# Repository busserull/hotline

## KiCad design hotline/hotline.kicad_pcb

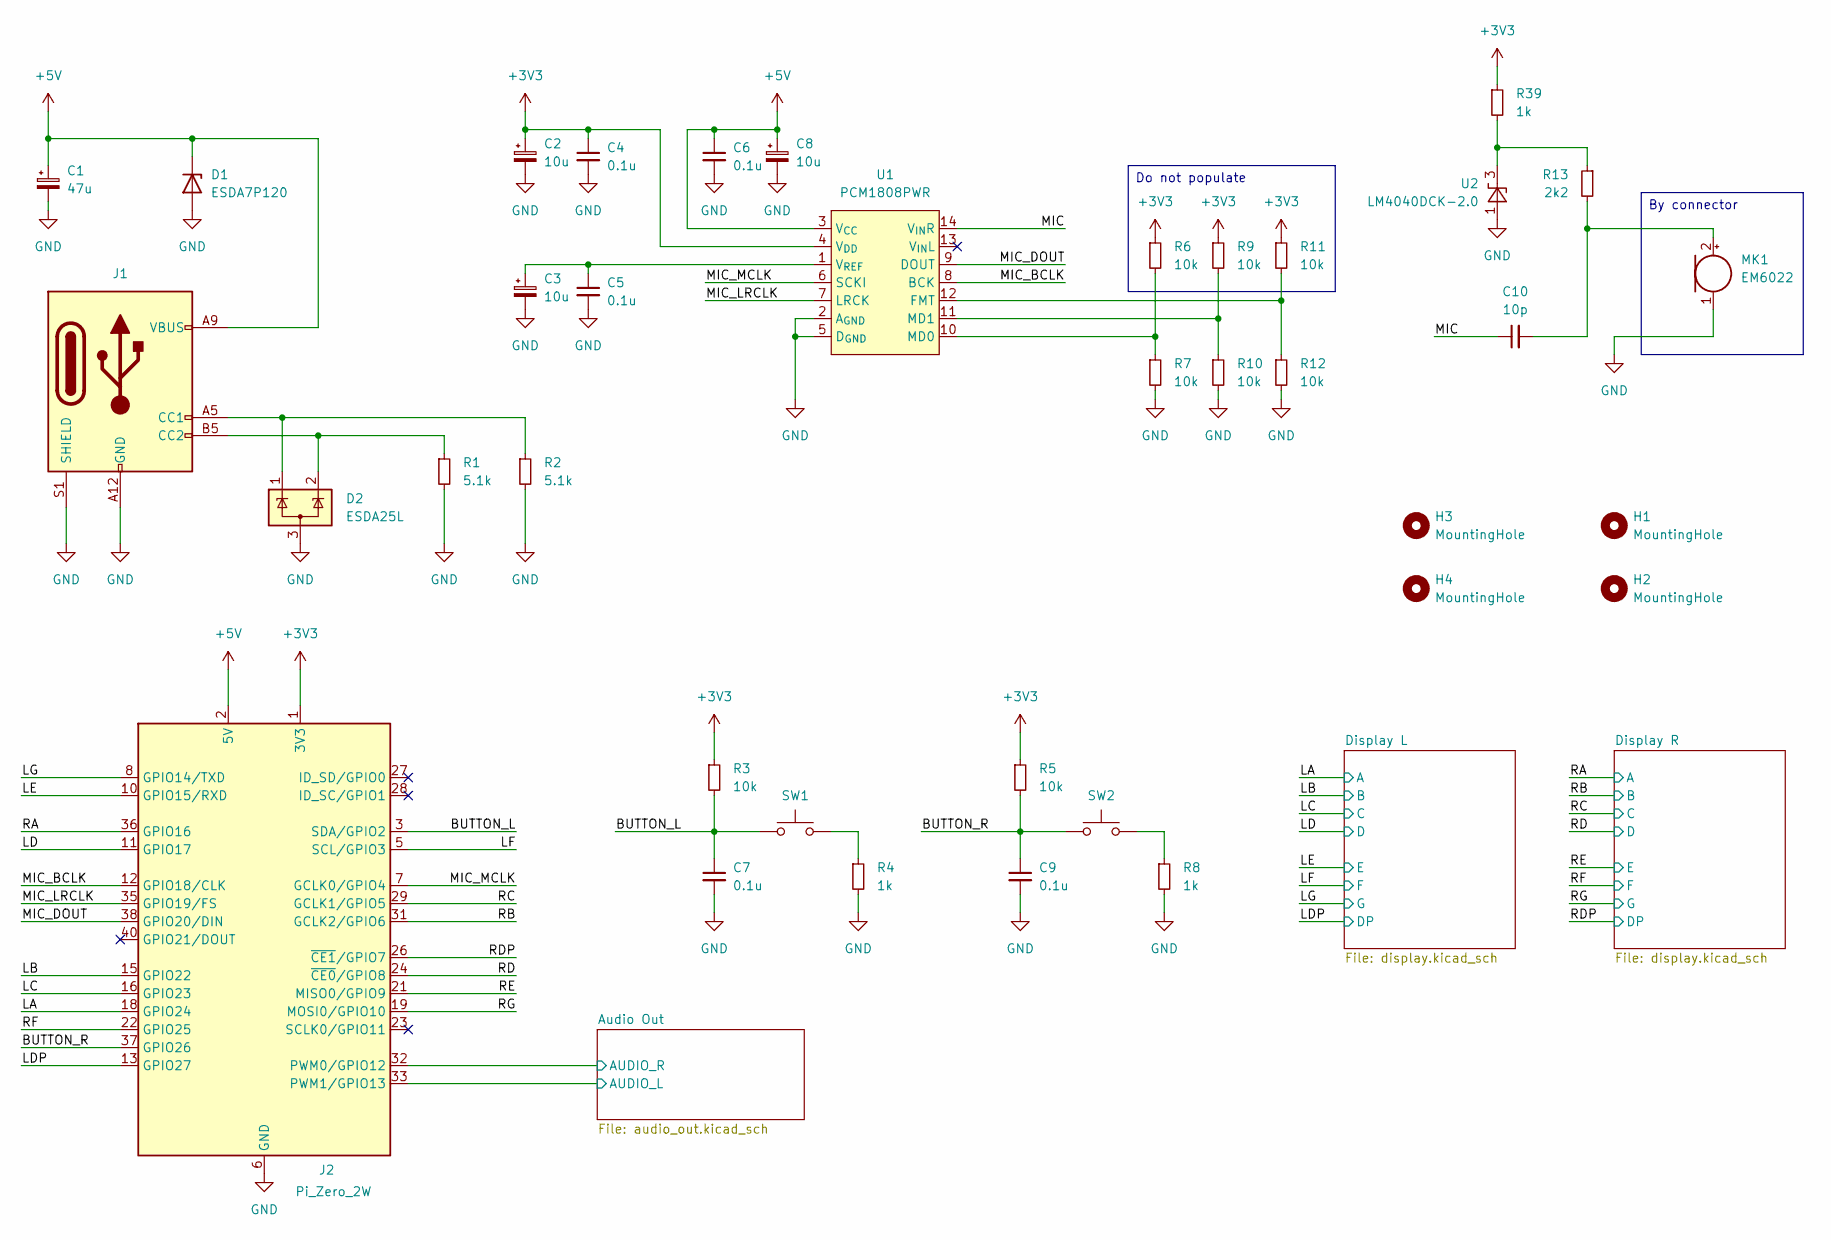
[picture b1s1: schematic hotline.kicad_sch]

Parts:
C1: 47u; CP_Elec_6.3x7.7
C2, C3, C8: 10u; CP_Elec_4x5.7
C4, C5, C6, C7, C9: 0.1u; C_0603_1608Metric_Pad1.08x0.95mm_HandSolder
C10: 10p; C_0603_1608Metric_Pad1.08x0.95mm_HandSolder
D1: ESDA7P120; D_0603_1608Metric_Pad1.05x0.95mm_HandSolder
D2: ESDA25L; SOT-23-3
H1, H2, H3, H4: MountingHole; MountingHole_2.2mm_M2_ISO7380_Pad
J1: USB_C_Receptacle_PowerOnly_24P; USB_C_Receptacle_HRO_TYPE-C-31-M-17
J2: Pi_Zero_2W; PinHeader_2x20_P2.54mm_Vertical
MK1: EM6022; TerminalBlock_Phoenix_PT-1,5-2-5.0-H_1x02_P5.00mm_Horizontal
R1, R2: 5.1k; R_0603_1608Metric_Pad0.98x0.95mm_HandSolder
R3, R5, R6, R7, R9, R10, R11, R12: 10k; R_0603_1608Metric_Pad0.98x0.95mm_HandSolder
R4, R8, R39: 1k; R_0603_1608Metric_Pad0.98x0.95mm_HandSolder
R13: 2k2; R_0603_1608Metric_Pad0.98x0.95mm_HandSolder
SW1: Left; TerminalBlock_Phoenix_PT-1,5-2-5.0-H_1x02_P5.00mm_Horizontal
SW2: Right; TerminalBlock_Phoenix_PT-1,5-2-5.0-H_1x02_P5.00mm_Horizontal
U1: PCM1808PWR; TSSOP-14_4.4x5mm_P0.65mm
U2: LM4040DCK-2.0; SOT-353_SC-70-5

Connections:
+3V3: C2.1, C4.1, J2.1 (3V3), J2.17 (3V3), R3.1, R5.1, R6.1, R9.1, R11.1, R39.1, U1.4 (V_{DD}); also elsewhere on the board
+5V: C1.1, C6.1, C8.1, D1.1 (K), J1.A4 (VBUS), J1.A9 (VBUS), J1.B4 (VBUS), J1.B9 (VBUS), J2.2 (5V), J2.4 (5V), U1.3 (V_{CC}); also elsewhere on the board
/Audio Out/AUDIO_L: J2.33 (PWM1/GPIO13); also elsewhere on the board
/Audio Out/AUDIO_R: J2.32 (PWM0/GPIO12); also elsewhere on the board
/BUTTON_L: C7.1, J2.3 (SDA/GPIO2), R3.2, SW1.1
/BUTTON_R: C9.1, J2.37 (GPIO26), R5.2, SW2.1
/LA: J2.18 (GPIO24); also elsewhere on the board
/LB: J2.15 (GPIO22); also elsewhere on the board
/LC: J2.16 (GPIO23); also elsewhere on the board
/LD: J2.11 (GPIO17); also elsewhere on the board
/LDP: J2.13 (GPIO27); also elsewhere on the board
/LE: J2.10 (GPIO15/RXD); also elsewhere on the board
/LF: J2.5 (SCL/GPIO3); also elsewhere on the board
/LG: J2.8 (GPIO14/TXD); also elsewhere on the board
/MIC: C10.1, U1.14 (V_{IN}R)
/MIC_BCLK: J2.12 (GPIO18/CLK), U1.8 (BCK)
/MIC_DOUT: J2.38 (GPIO20/DIN), U1.9 (DOUT)
/MIC_LRCLK: J2.35 (GPIO19/FS), U1.7 (LRCK)
/MIC_MCLK: J2.7 (GCLK0/GPIO4), U1.6 (SCKI)
/RA: J2.36 (GPIO16); also elsewhere on the board
/RB: J2.31 (GCLK2/GPIO6); also elsewhere on the board
/RC: J2.29 (GCLK1/GPIO5); also elsewhere on the board
/RD: J2.24 (~CE0/GPIO8); also elsewhere on the board
/RDP: J2.26 (~CE1/GPIO7); also elsewhere on the board
/RE: J2.21 (MISO0/GPIO9); also elsewhere on the board
/RF: J2.22 (GPIO25); also elsewhere on the board
/RG: J2.19 (MOSI0/GPIO10); also elsewhere on the board
GND: C1.2, C2.2, C3.2, C4.2, C5.2, C6.2, C7.2, C8.2, C9.2, D1.2 (A), D2.3 (A), J1.A1 (GND), J1.A12 (GND), J1.B1 (GND), J1.B12 (GND), J1.S1 (SHIELD), J2.6 (GND), J2.9 (GND), J2.14 (GND), J2.20 (GND), J2.25 (GND), J2.30 (GND), J2.34 (GND), J2.39 (GND), MK1.1 (-), R1.2, R2.2, R4.2, R7.2, R8.2, R10.2, R12.2, U1.2 (A_{GND}), U1.5 (D_{GND}), U2.1 (A); also elsewhere on the board
unnamed: D2.1 (K), J1.A5 (CC1), R2.1
unnamed: D2.2 (K), J1.B5 (CC2), R1.1
unnamed: C10.2, MK1.2 (+), R13.2
unnamed: R4.1, SW1.2
unnamed: R8.1, SW2.2
unnamed: R11.2, R12.1, U1.12 (FMT)
unnamed: R6.2, R7.1, U1.10 (MD0)
unnamed: R9.2, R10.1, U1.11 (MD1)
unnamed: C3.1, C5.1, U1.1 (V_{REF})
unnamed: R13.1, R39.2, U2.3 (K)

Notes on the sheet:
By connector
Do not populate

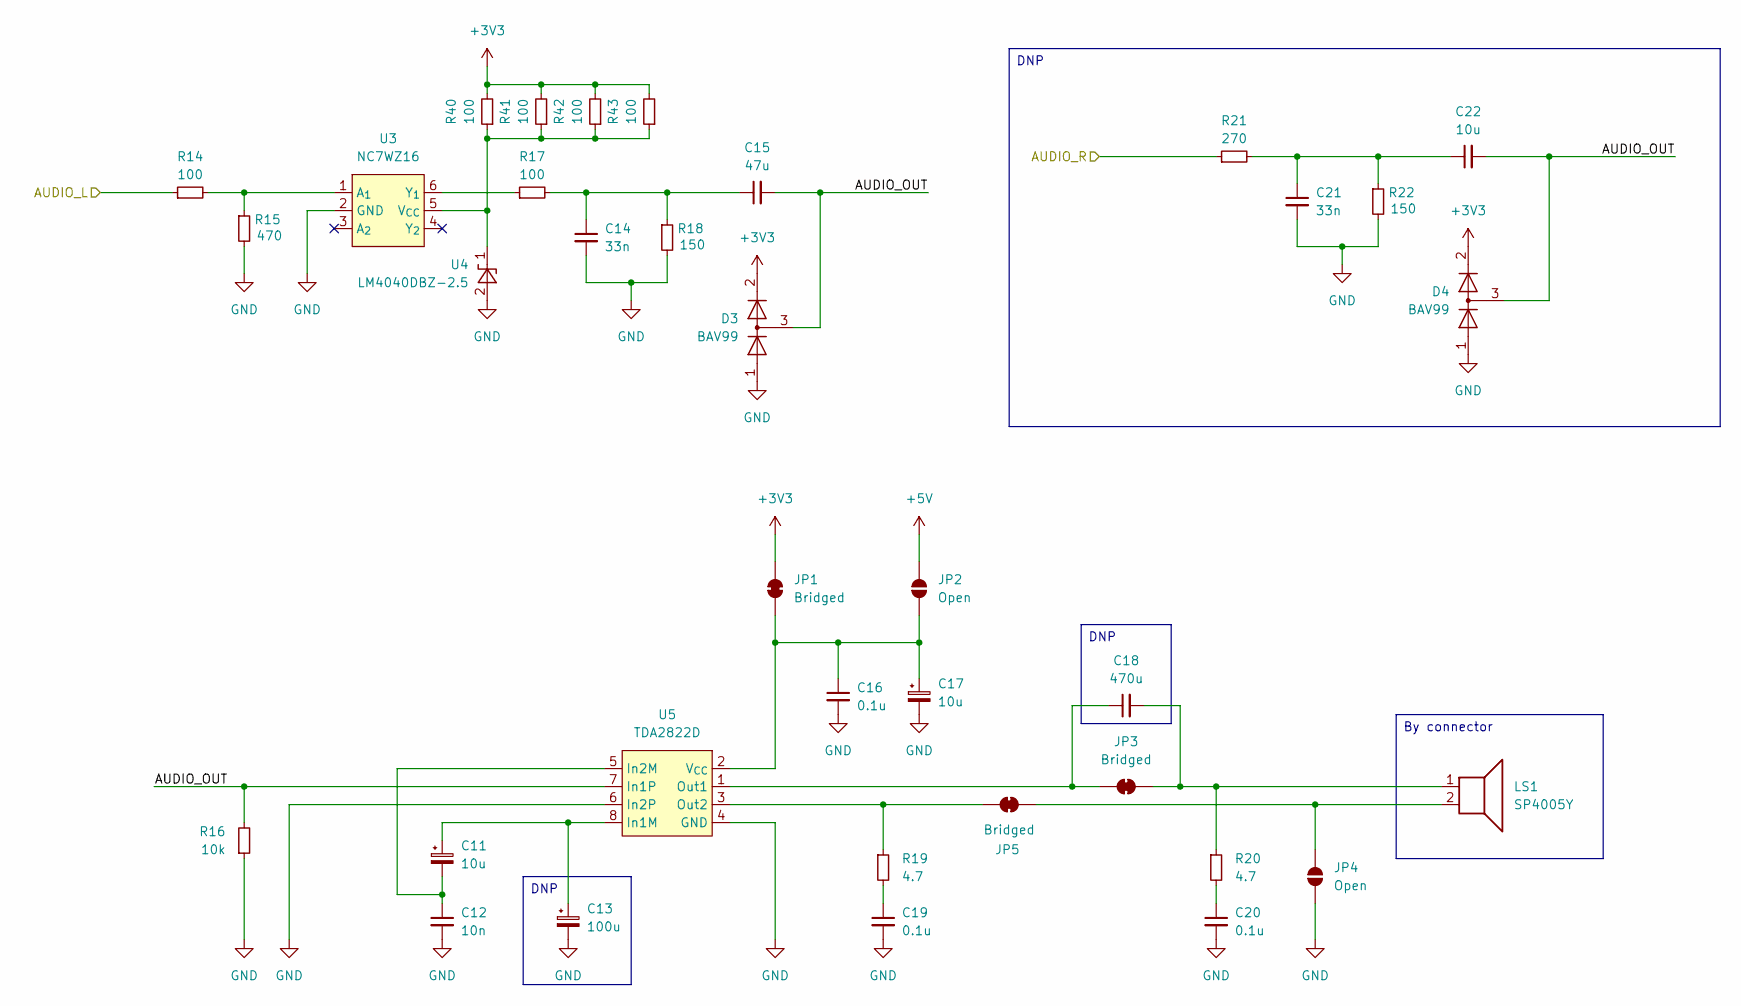
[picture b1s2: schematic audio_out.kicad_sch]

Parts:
C11, C17: 10u; CP_Elec_4x5.7
C12: 10n; C_0603_1608Metric_Pad1.08x0.95mm_HandSolder
C13: 100u; CP_Elec_5x5.3
C14, C21: 33n; C_0603_1608Metric_Pad1.08x0.95mm_HandSolder
C15: 47u; C_0805_2012Metric_Pad1.18x1.45mm_HandSolder
C16, C19, C20: 0.1u; C_0603_1608Metric_Pad1.08x0.95mm_HandSolder
C18: 470u; CP_Elec_8x10
C22: 10u; C_0805_2012Metric_Pad1.18x1.45mm_HandSolder
D3, D4: BAV99; SOT-23
JP1, JP3, JP5: Bridged; SolderJumper-2_P1.3mm_Bridged_RoundedPad1.0x1.5mm
JP2, JP4: Open; SolderJumper-2_P1.3mm_Open_RoundedPad1.0x1.5mm
LS1: SP4005Y; TerminalBlock_Phoenix_PT-1,5-2-5.0-H_1x02_P5.00mm_Horizontal
R14, R17, R40, R41, R42, R43: 100; R_0603_1608Metric_Pad0.98x0.95mm_HandSolder
R15: 470; R_0603_1608Metric_Pad0.98x0.95mm_HandSolder
R16: 10k; R_0603_1608Metric_Pad0.98x0.95mm_HandSolder
R18, R22: 150; R_0603_1608Metric_Pad0.98x0.95mm_HandSolder
R19, R20: 4.7; R_0603_1608Metric_Pad0.98x0.95mm_HandSolder
R21: 270; R_0603_1608Metric_Pad0.98x0.95mm_HandSolder
U3: NC7WZ16; SOT-363_SC-70-6_Handsoldering
U4: LM4040DBZ-2.5; SOT-23
U5: TDA2822D; SOIC-8_3.9x4.9mm_P1.27mm

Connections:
+3V3: D3.2 (A), D4.2 (A), JP1.2 (B), R40.2, R41.2, R42.2, R43.2; also elsewhere on the board
+5V: JP2.2 (B); also elsewhere on the board
/Audio Out/AUDIO_L: R14.1; also elsewhere on the board
/Audio Out/AUDIO_OUT: C15.2, C22.2, D3.3 (K), D4.3 (K), R16.2, U5.7 (In1P)
/Audio Out/AUDIO_R: R21.1; also elsewhere on the board
GND: C12.2, C13.2, C14.2, C16.2, C17.2, C19.2, C20.2, C21.2, D3.1 (K), D4.1 (K), JP4.1 (A), R15.2, R16.1, R18.2, R22.2, U3.2 (GND), U4.2 (A), U5.4 (GND), U5.6 (In2P); also elsewhere on the board
unnamed: C14.1, C15.1, R17.2, R18.1
unnamed: C19.1, R19.2
unnamed: C20.1, R20.2
unnamed: C21.1, C22.1, R21.2, R22.1
unnamed: C16.1, C17.1, JP1.1 (A), JP2.1 (A), U5.2 (V_{CC})
unnamed: C18.2, JP3.1 (A), LS1.1, R20.1
unnamed: C18.1, JP3.2 (B), U5.1 (Out1)
unnamed: JP4.2 (B), JP5.1 (A), LS1.2
unnamed: JP5.2 (B), R19.1, U5.3 (Out2)
unnamed: R14.2, R15.1, U3.1 (A_{1})
unnamed: R40.1, R41.1, R42.1, R43.1, U3.5 (V_{CC}), U4.1 (K)
unnamed: R17.1, U3.6 (Y_{1})
unnamed: C11.1, C13.1, U5.8 (In1M)
unnamed: C11.2, C12.1, U5.5 (In2M)

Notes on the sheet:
DNP
By connector

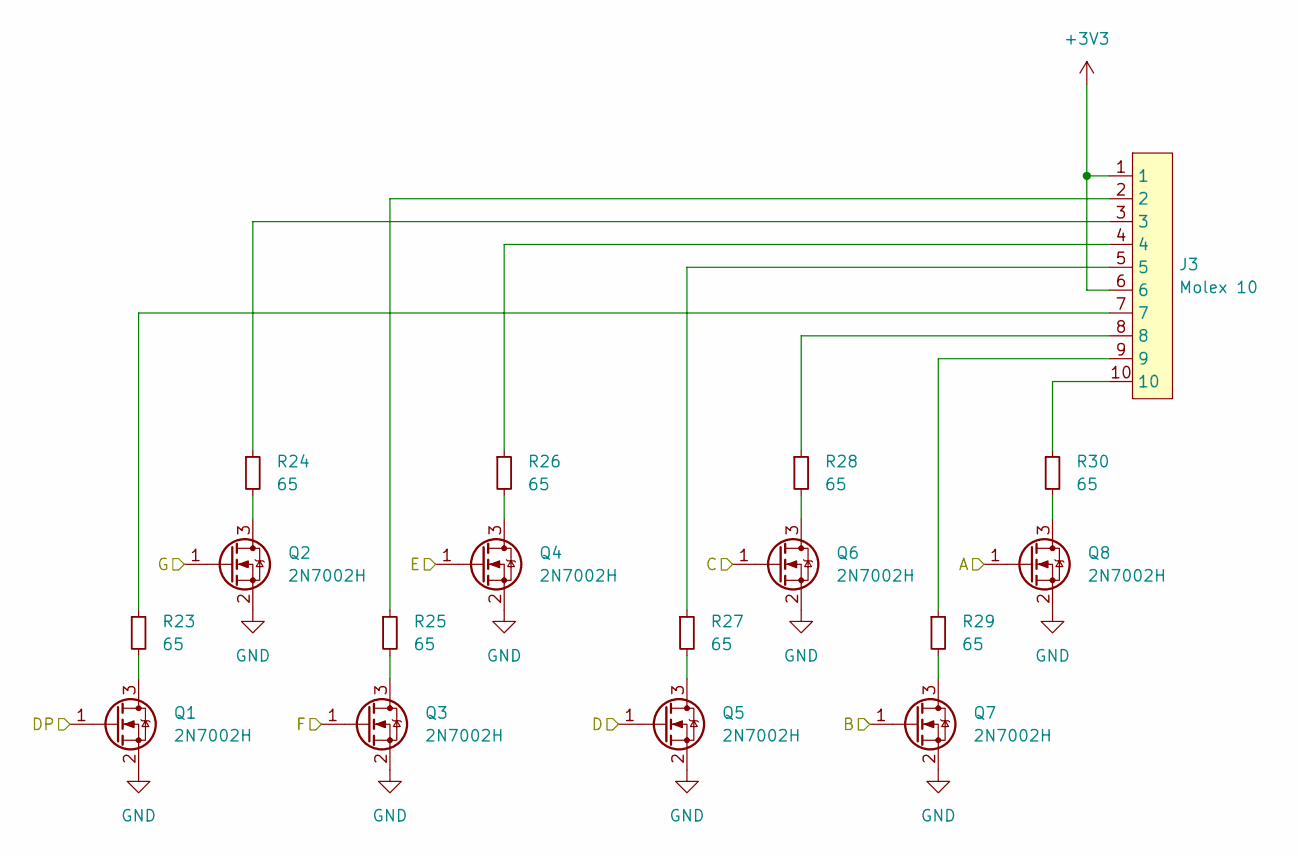
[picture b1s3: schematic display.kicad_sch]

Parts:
J3: Molex 10; Molex_PicoBlade_53261-1071_1x10-1MP_P1.25mm_Horizontal
Q1, Q2, Q3, Q4, Q5, Q6, Q7, Q8: 2N7002H; SOT-23
R23, R24, R25, R26, R27, R28, R29, R30: 65; R_0603_1608Metric_Pad0.98x0.95mm_HandSolder

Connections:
+3V3: J3.1, J3.6; also elsewhere on the board
/RA: Q8.1 (G); also elsewhere on the board
/RB: Q7.1 (G); also elsewhere on the board
/RC: Q6.1 (G); also elsewhere on the board
/RD: Q5.1 (G); also elsewhere on the board
/RDP: Q1.1 (G); also elsewhere on the board
/RE: Q4.1 (G); also elsewhere on the board
/RF: Q3.1 (G); also elsewhere on the board
/RG: Q2.1 (G); also elsewhere on the board
GND: Q1.2 (S), Q2.2 (S), Q3.2 (S), Q4.2 (S), Q5.2 (S), Q6.2 (S), Q7.2 (S), Q8.2 (S); also elsewhere on the board
unnamed: J3.2, R25.1
unnamed: J3.3, R24.1
unnamed: J3.4, R26.1
unnamed: J3.5, R27.1
unnamed: J3.7, R23.1
unnamed: J3.8, R28.1
unnamed: J3.9, R29.1
unnamed: J3.10, R30.1
unnamed: Q1.3 (D), R23.2
unnamed: Q2.3 (D), R24.2
unnamed: Q3.3 (D), R25.2
unnamed: Q4.3 (D), R26.2
unnamed: Q5.3 (D), R27.2
unnamed: Q6.3 (D), R28.2
unnamed: Q7.3 (D), R29.2
unnamed: Q8.3 (D), R30.2

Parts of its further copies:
J4: Molex 10; Molex_PicoBlade_53261-1071_1x10-1MP_P1.25mm_Horizontal
Q9, Q10, Q11, Q12, Q13, Q14, Q15, Q16: 2N7002H; SOT-23
R31, R32, R33, R34, R35, R36, R37, R38: 65; R_0603_1608Metric_Pad0.98x0.95mm_HandSolder

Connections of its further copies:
+3V3: J4.1, J4.6; also elsewhere on the board
/LA: Q16.1 (G); also elsewhere on the board
/LB: Q15.1 (G); also elsewhere on the board
/LC: Q14.1 (G); also elsewhere on the board
/LD: Q13.1 (G); also elsewhere on the board
/LDP: Q9.1 (G); also elsewhere on the board
/LE: Q12.1 (G); also elsewhere on the board
/LF: Q11.1 (G); also elsewhere on the board
/LG: Q10.1 (G); also elsewhere on the board
GND: Q9.2 (S), Q10.2 (S), Q11.2 (S), Q12.2 (S), Q13.2 (S), Q14.2 (S), Q15.2 (S), Q16.2 (S); also elsewhere on the board
unnamed: J4.2, R33.1
unnamed: J4.3, R32.1
unnamed: J4.4, R34.1
unnamed: J4.5, R35.1
unnamed: J4.7, R31.1
unnamed: J4.8, R36.1
unnamed: J4.9, R37.1
unnamed: J4.10, R38.1
unnamed: Q9.3 (D), R31.2
unnamed: Q10.3 (D), R32.2
unnamed: Q11.3 (D), R33.2
unnamed: Q12.3 (D), R34.2
unnamed: Q13.3 (D), R35.2
unnamed: Q14.3 (D), R36.2
unnamed: Q15.3 (D), R37.2
unnamed: Q16.3 (D), R38.2

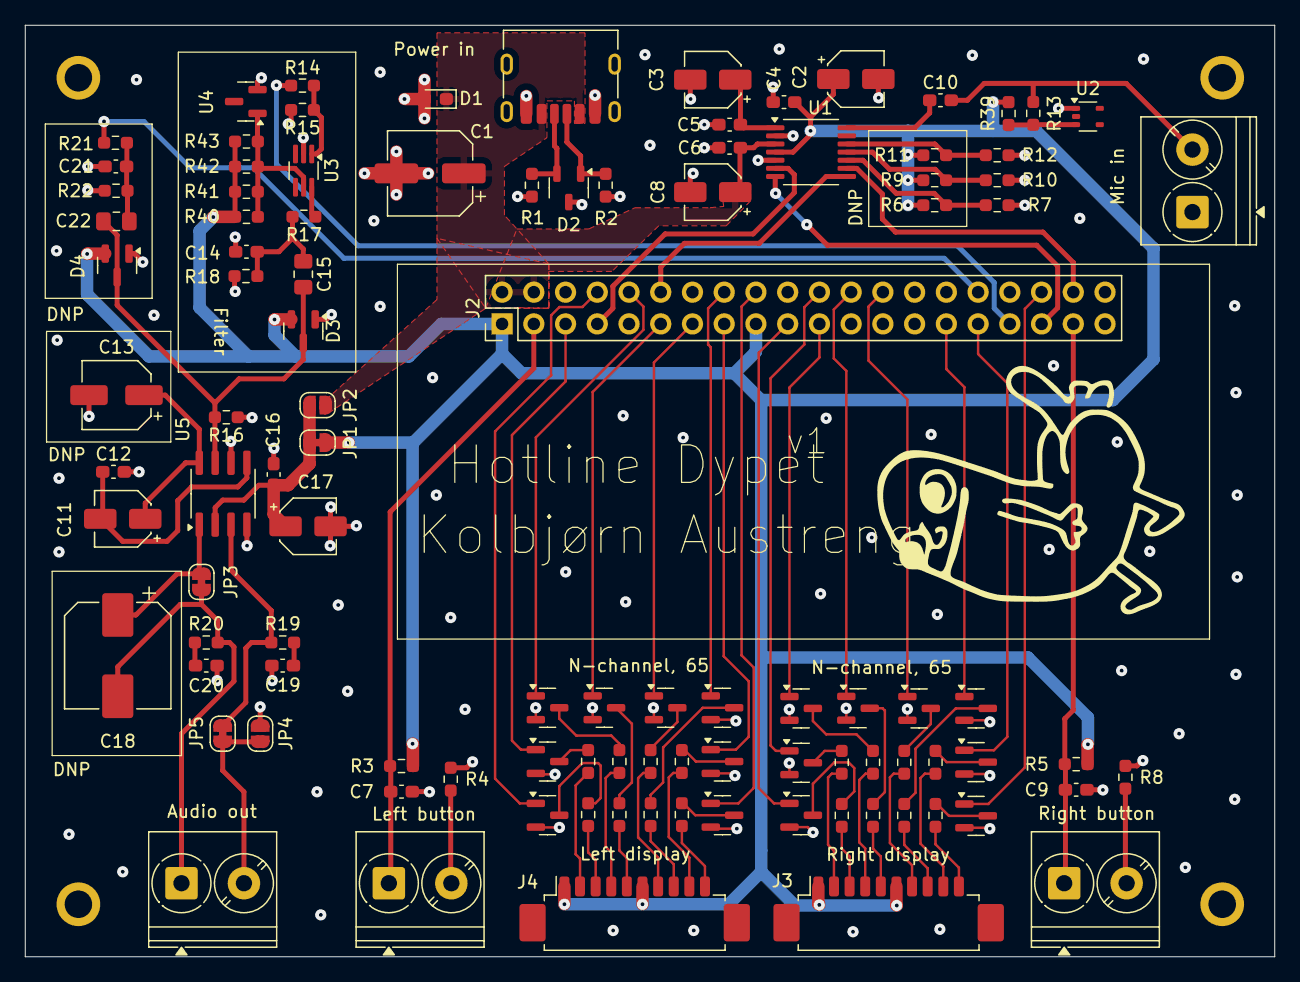
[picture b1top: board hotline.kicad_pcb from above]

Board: 4 copper layers, 100.0 x 74.5 mm, 107 parts (0 on the bottom side), 85 nets.

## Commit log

2025-03-07 init commit
2025-03-08 assign footprints
2025-03-09 place components
2025-03-09 4 layers
